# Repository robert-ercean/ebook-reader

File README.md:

# Block Diagram

# Hardware Features – Detailed Description

## 1. Microcontroller – ESP32-C6

- **Processor:** 32-bit RISC-V core, clocked up to 160 MHz.
- **Memory:** 512KB internal SRAM and 8MB external flash memory (model W25Q512JVEIQ).
- **Connectivity:** Supports Wi-Fi 6 (802.11ax), Bluetooth Low Energy 5, and USB 2.0 (full-speed).
- **Interfaces:** SPI, I²C, UART, and multiple available GPIOs.
- **Power Efficiency:** Power-saving modes, including deep sleep.

## 2. E-Paper Display – 7.5”

- **Model:** Waveshare or equivalent, with a resolution of 800×480 pixels.
- **Connection:** 4-wire SPI plus control pins (CS, DC, RST, BUSY).
- **Power Consumption:** Very low in static mode; during refresh, consumption ranges between 15–25mA.

## 3. Environmental Sensor – BME688

- **Measurements:** Temperature, relative humidity, atmospheric pressure, and air quality (eCO2/VOC).
- **Interface:** I²C protocol at 400kHz (SDA/SCL).
- **Power Consumption:** Approx. 2.1µA in standby, with peaks of a few mA when active.

## 4. Power Supply and Management System

- **Battery:** Li-Po 3.7V, 2500mAh capacity.
- **Charging:** MCP73831 – simple and reliable IC for USB-C charging, up to 1A.
- **Monitoring:** MAX17048 – fuel gauge providing voltage and battery level data.
- **Voltage Regulation:** LDO such as XC6220A331MR-G, for a stable 3.3V output.

**Why these components?**
- MCP73831 offers a compact and efficient solution.
- MAX17048 enables precise battery monitoring and low-level warnings.

## 5. Buttons – 3 units

- **Type:** Tactile switch (Panasonic or similar).
- **Purpose:** Menu navigation, page turning, option selection.
- **Connection:** To GPIOs, with hardware (RC) or software debouncing.

## 6. USB-C Connector

- **Purpose:** Power/charging + data transfer via USB 2.0.
- **Protection:** ESD (e.g., USBLC6-2SC6Y) and termination resistors.
- **Options:** Supports firmware updates via USB or OTA via Wi-Fi.

## 7. Qwiic Interface (I²C)

- **Pins:** VCC, GND, SDA, SCL.
- **Functionality:** Quick expansion with additional I²C sensors/modules.

## 8. SD Card Slot – 112A-TAAR-R03

- **Purpose:** Storing e-books, logs, or firmware files.
- **Connection:** SPI or SDIO, depending on implementation.

## 9. Real-Time Clock – DS3231

- **Purpose:** Precise timekeeping, even without main power.
- **Communication:** I²C (shared with other sensors).
- **Backup:** Supercapacitor or secondary battery.

## 10. Additional Memory

- **Model:** W25Q512JVEIQ – external flash memory.
- **Connection:** Dedicated SPI (quad SPI) for firmware and large files.

---

# 4. ESP32-C6 Pin Allocation

| ESP32-C6 Pin | Signal                        | Detailed                                   |
|--------------|-------------------------------|--------------------------------------------|
| GPIO1        | I²C SDA                       | Data line for sensors and RTC              |
| GPIO2        | I²C SCL                       | Clock line for I²C interface               |
| GPIO5        | SPI MISO                      | Data input from e-paper                    |
| GPIO6        | SPI MOSI                      | Data output to e-paper                     |
| GPIO7        | SPI CLK                       | Clock signal for SPI                       |
| GPIO8        | SPI CS (e-paper)              | Chip select for display                    |
| GPIO9        | E-paper DC                    | Switch between data and command modes      |
| GPIO10       | E-paper RST                   | Hardware reset for the display             |
| GPIO11       | E-paper BUSY                  | Status signal (busy/free)                  |
| GPIO12       | Button 1                      | Digital input for NEXT                     |
| GPIO13       | Button 2                      | Digital input for PREV                     |
| GPIO14       | Button 3                      | Digital input for OK/MENU                  |
| GPIO15       | MAX17048 ALERT (optional)     | Low battery alert                          |
| GPIO16       | USB D+                        | USB data line (fixed pin)                  |
| GPIO17       | USB D-                        | USB data line (fixed pin)                  |
| GPIO18       | Status LED (optional)         | Visual indicator for various states        |
| GPIO19       | SD Card CS                    | Chip select for SD card (SPI)              |
| GPIO20       | SD Card MISO                  | Data received from SD card                 |
| GPIO21       | SD Card MOSI                  | Data sent to SD card                       |
| GPIO4        | SD Card CLK                   | SPI clock line for SD communication        |

---

# Power Consumption Estimate

| Module                | Typical Consumption              |
|------------------------|----------------------------------|
| ESP32-C6 active        | ~80mA with Wi-Fi / <10mA idle   |
| E-paper (refresh)      | 15–25mA                         |
| BME688 active          | up to 3.6mA / 2.1µA standby     |
| MAX17048               | Approx. 50µA                    |
| DS3231                 | ~3.5mA active / <1µA backup     |
| MCP73831               | Varies based on charging current|

**Usage Scenarios:**
- In **deep sleep**, total consumption can drop below 100µA.
- In active mode with Wi-Fi and screen refresh, consumption may reach 100–150mA.
- A 2500mAh battery allows for **weeks of operation** in predominantly passive mode (static display, infrequent Wi-Fi activity).

---

# Bill of Materials:

| Component | Type | Marketplace | Datasheet |
|----------|------|-------------|-----------|
| EAGLE-LTSPICE_CC0402 | Capacitor | [Link](https://eu.mouser.com/ProductDetail/KEMET/C0402C475K8PACTU?qs=ulEaXIWI0c9ebKRT3r3htg%3D%3D) | [Datasheet](https://eu.mouser.com/datasheet/2/447/KEM_C1006_X5R_SMD-3316465.pdf) |
| ESP32_WROVER_EAGLE-LTSPICE_RR0402 | Resistor | [Link](https://eu.mouser.com/ProductDetail/Vishay-Beyschlag/MCS04020D9101BE000?qs=sGAEpiMZZMvdGkrng054twKDKoBh%252BscnK%2FuqkNk9X%252BqO%2Fz5%2F0u93Ow%3D%3D) | [Datasheet](https://www.vishay.com/docs/28700/mcx0x0xpre.pdf) |
| RCL_CPOL-EUCT3528 | Capacitor | [Link](https://eu.mouser.com/ProductDetail/Nichicon/LGN2W101MELA25?qs=Fe64Qgzkstf1zMszMsgRoA%3D%3D) | [Datasheet](https://eu.mouser.com/datasheet/2/293/e_lgn-3082370.pdf) |
| ADAFRUIT_LEDCHIP-LED0603 | LED | [Link](https://eu.mouser.com/ProductDetail/ams-OSRAM/KG-EELP41.22-PHRH-35-A8J8-20-R18?qs=ZcfC38r4Posajg8ZvCDQkg%3D%3D) | [Datasheet](https://eu.mouser.com/datasheet/2/588/KG_EELP41_22_EN-3572852.pdf) |
| CPH3225A | Capacitor | [Link](https://eu.mouser.com/ProductDetail/Seiko-Semiconductors/CPH3225A?qs=3etwrb1wR%252BhUOph6lAO7eg%3D%3D) | [Datasheet](https://eu.mouser.com/datasheet/2/360/Seiko_Instruments_MicroBattery_E_20230330_2024Jan_-3561061.pdf) |
| ESP32_WROVER_SPARKFUN-DISCRETESEMI_MOSFET_PCH-DMG2305UX-7 | Transistor | [Link](https://eu.mouser.com/ProductDetail/Diodes-Incorporated/DMG2305UX-7?qs=L1DZKBg7t5F%2FNBHrjfxC%252Bg%3D%3D) | [Datasheet](https://www.diodes.com/assets/Datasheets/DMG2305UX.pdf) |
| ESP32_WROVER_AVX---SD0805S020S1R0_AVX_SD0805S020S1R0_0_0AVX_SD0805S020S1R0_0_0 | Diode | [Link](https://eu.mouser.com/ProductDetail/ROHM-Semiconductor/SCS310AMC7G?qs=iLKYxzqNS75xiccEgNnX2g%3D%3D) | [Datasheet](https://fscdn.rohm.com/en/products/databook/datasheet/discrete/sic/sbd/scs310am-e.pdf) |
| SI1308EDL-T1-GE3 | Transistor | [Link](https://eu.mouser.com/ProductDetail/Vishay-Semiconductors/SI1308EDL-T1-GE3?qs=bX1%252BNvsK%2FBramh9tgpOaEw%3D%3D) | [Datasheet](https://www.vishay.com/docs/63399/si1308edl.pdf) |
| ESP32C6_VARISTORCN1812 | Varistor | [Link](https://eu.mouser.com/ProductDetail/Schurter/PFMF.050.2?qs=1auRipcfynCums5v1iucSA%3D%3D) | [Datasheet](https://eu.mouser.com/datasheet/2/358/typ_PFMF-1275918.pdf) |
| ESP32_WROVER_BME680_BME680 | Integrated Environmental Unit | [Link](https://eu.mouser.com/ProductDetail/M5Stack/U001-C?qs=e8oIoAS2J1R2mB7ZY1%252BSZg%3D%3D) | [Datasheet](https://docs.m5stack.com/en/unit/envIII) |
| ESP32-C6-WROOM-1-N8 | MicroController | [Link](https://eu.mouser.com/ProductDetail/Espressif-Systems/ESP32-C6?qs=Imq1NPwxi75noDtUpuVuWw%3D%3D) | [Datasheet](https://eu.mouser.com/datasheet/2/891/esp32_c6_datasheet_en-3304070.pdf) |
| 744043680IND_4828-WE-TPC_WRE | Inductor | [Link](https://eu.mouser.com/ProductDetail/Wurth-Elektronik/744043680?qs=PGXP4M47uW6VkZq%252BkzjrHA%3D%3D) | [Datasheet](https://www.we-online.com/components/products/datasheet/744043680.pdf) |
| SI1308EDL-T1-GE3 | Transistor | [Link](https://eu.mouser.com/ProductDetail/Vishay-Semiconductors/SI1308EDL-T1-GE3?qs=bX1%252BNvsK%2FBramh9tgpOaEw%3D%3D) | [Datasheet](https://www.vishay.com/docs/63399/si1308edl.pdf) |
| BD5229G-TR | Voltage Detector | [Link](https://eu.mouser.com/ProductDetail/ROHM-Semiconductor/BD5229G-TR?qs=sGAEpiMZZMutXGli8Ay4kAMqIQqqdOUlDFcDfPDPIK4%3D) | [Datasheet](https://fscdn.rohm.com/en/products/databook/datasheet/ic/power/voltage_detector/bd52xxg-e.pdf) |
| DS3231SN# | RTC Module | [Link](https://eu.mouser.com/ProductDetail/Analog-Devices-Maxim-Integrated/DS3231SN?qs=1eQvB6Dk1vhUlr8%2FOrV0Fw%3D%3D) | [Datasheet](https://eu.mouser.com/datasheet/2/609/DS3231-3421123.pdf) |
| USBLC6-2SC6Y | ESD Protection | [Link](https://eu.mouser.com/ProductDetail/STMicroelectronics/USBLC6-2SC6Y?qs=gNDSiZmRJS%2FOgDexvXkdow%3D%3D) | [Datasheet](https://eu.mouser.com/datasheet/2/389/usblc6_2sc6y-1852505.pdf) |
| W25Q512JVEIQ | Flash Memory | [Link](https://eu.mouser.com/ProductDetail/Winbond/W25Q512JVEIQ?qs=l7cgNqFNU1jw6svr3at6tA%3D%3D) | [Datasheet](https://eu.mouser.com/datasheet/2/949/Winbond_W25Q512JV_Datasheet-3240039.pdf) |
| SAMACSYS_PARTS_USB4110-GF-A | USB Connector | [Link](https://eu.mouser.com/ProductDetail/GCT/USB4110-GF-A?qs=KUoIvG%2F9IlYiZvIXQjyJeA%3D%3D) | [Datasheet](https://eu.mouser.com/datasheet/2/837/GCT_USB4110_Product_Drawing___20k_cycles-3455479.pdf) |
| FH34SRJ | E-Paper Display Header | [Link](https://eu.mouser.com/ProductDetail/Hirose-Connector/FH34SRJ-7S-0.5SH50?qs=vcbW%252B4%252BSTIqHa4IamMh36g%3D%3D) | [Datasheet](https://eu.mouser.com/datasheet/2/185/FH34SRJ_7S_0_5SH_50__CL0580_1200_0_50_2DDrawing_00-1615127.pdf) |
| MAX17048G+T10 | Battery Management | [Link](https://eu.mouser.com/ProductDetail/Analog-Devices-Maxim-Integrated/MAX17048G%2bT10?qs=D7PJwyCwLAoGnnn8jEPRBQ%3D%3D) | [Datasheet](https://eu.mouser.com/datasheet/2/609/MAX17048_MAX17049-3469099.pdf) |
| MCP73831 | Battery Controller | [Link](https://eu.mouser.com/ProductDetail/Microchip-Technology/MCP73831T-2ATI-MC?qs=yUQqVecv4qs9k7ug0bEXiw%3D%3D) | [Datasheet](https://eu.mouser.com/datasheet/2/268/MCP73831_Family_Data_Sheet_DS20001984H-3441711.pdf) |
| 112A-TAAR-R03_ATTEND | SD Card Mount | [Link](https://store.comet.srl.ro/Catalogue/Product/43497/) | [Datasheet](https://store.comet.srl.ro/Catalogue/Product/43497/) |
| XC6220A331MR-G | LDO Voltage Regulator | [Link](https://eu.mouser.com/ProductDetail/Torex-Semiconductor/XC6220A331MR-G?qs=AsjdqWjXhJ8ZSWznL1J0gg%3D%3D) | [Datasheet](https://eu.mouser.com/datasheet/2/760/xc6220-3371556.pdf) |

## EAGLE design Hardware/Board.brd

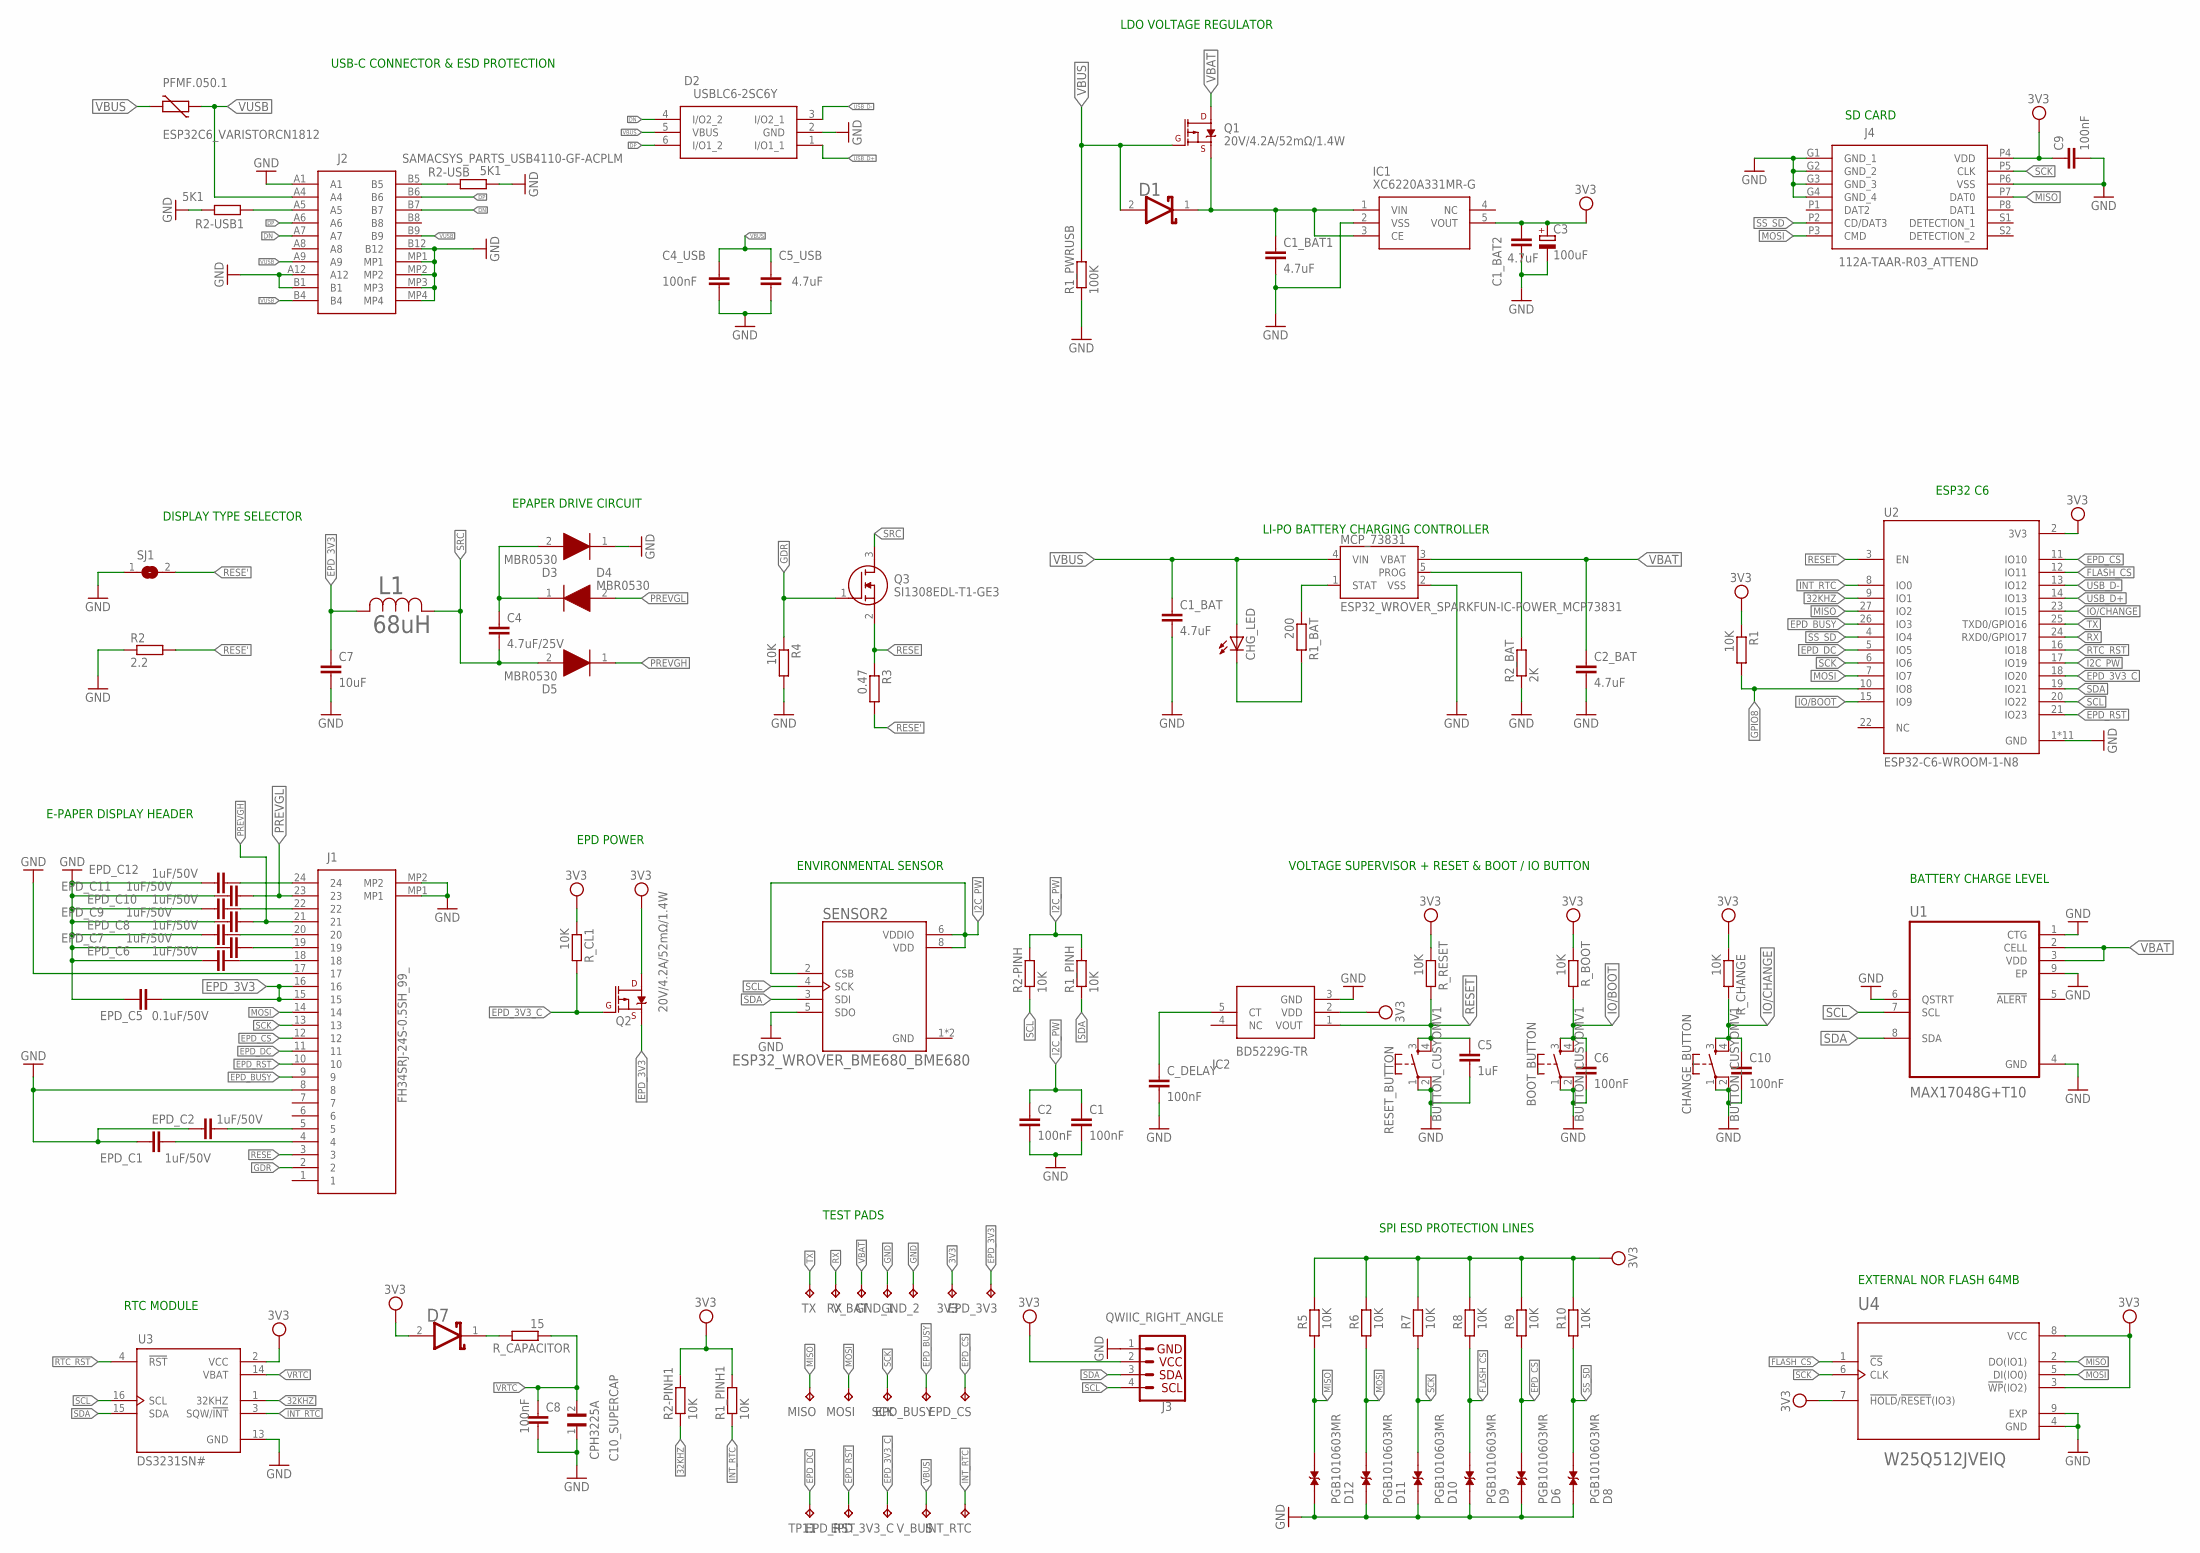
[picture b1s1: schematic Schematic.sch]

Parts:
3V3: TPTP20R; TP20R
BOOT_BUTTON: BUTTON_CUSYOMV1; MYBUTTON
C1, C2, C4_USB, C6, C8, C9, C10: 100nF; EAGLE-LTSPICE_C0402
C1_BAT, C1_BAT1, C1_BAT2, C2_BAT, C5_USB: 4.7uF; EAGLE-LTSPICE_C0402
C3: 100uF; RCL_CT3528
C4: 4.7uF/25V; EAGLE-LTSPICE_C0402
C5: 1uF; EAGLE-LTSPICE_C0402
C7: 10uF; EAGLE-LTSPICE_C0402
C10_SUPERCAP: CPH3225A; CAPCP3225X100N
CHANGE_BUTTON: BUTTON_CUSYOMV1; MYBUTTON
CHG_LED: ADAFRUIT_LEDCHIP-LED0603; ADAFRUIT_CHIP-LED0603
C_DELAY: 100nF; EAGLE-LTSPICE_C0402
D1, D7: ESP32_WROVER_AVX---SD0805S020S1R0_AVX_SD0805S020S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; ESP32_WROVER_AVX---SD0805S020S1R0_AVX_SD0805S020S1R0_0
D2: USBLC6-2SC6Y; SOT95P280X145-6N
D3, D4, D5: MBR0530; SOD3716X135N
D6, D8, D9, D10, D11, D12: PGB1010603MR; DIOC1608X36N
EPD_3V3, EPD_3V3_C: TPTP20R; TP20R
EPD_BUSY: TPTP20R; TP20R
EPD_C1, EPD_C2, EPD_C6, EPD_C7, EPD_C8, EPD_C9, EPD_C10, EPD_C11, EPD_C12: 1uF/50V; EAGLE-LTSPICE_C0402
EPD_C5: 0.1uF/50V; EAGLE-LTSPICE_C0402
EPD_CS: TPTP20R; TP20R
EPD_RST: TPTP20R; TP20R
GND_1, GND_2: TPTP20R; TP20R
IC1: XC6220A331MR-G; SOT95P280X120-5N
IC2: BD5229G-TR; SOT95P280X125-5N
INT_RTC: TPTP20R; TP20R
J1: FH34SRJ-24S-0.5SH_99_; FH34SRJ24S05SH99
J2: SAMACSYS_PARTS_USB4110-GF-ACPLM; SAMACSYS_PARTS_USB4110GFA
J3: QWIIC_RIGHT_ANGLE; JST04_1MM_RA
J4: 112A-TAAR-R03_ATTEND; 112ATAARR03ATTEND
L1: 68uH; IND_4828-WE-TPC_WRE
MCP_73831: ESP32_WROVER_SPARKFUN-IC-POWER_MCP73831; ESP32_WROVER_SPARKFUN-IC-POWER_SOT23-5
MISO: TPTP20R; TP20R
MOSI: TPTP20R; TP20R
PFMF.050.1: ESP32C6_VARISTORCN1812; ESP32C6_VARISTOR_CT/CN1812
Q1, Q2: 20V/4.2A/52mΩ/1.4W; ESP32_WROVER_SPARKFUN-DISCRETESEMI_SOT23-3
Q3: SI1308EDL-T1-GE3; SOT65P210X110-3N
R1, R1_PINH, R1_PINH1, R2-PINH, R2-PINH1, R4, R5, R6, R7, R8, R9, R10: 10K; ESP32_WROVER_EAGLE-LTSPICE_R0402
R1_BAT: 200; ESP32_WROVER_EAGLE-LTSPICE_R0402
R1_PWRUSB: 100K; ESP32_WROVER_EAGLE-LTSPICE_R0402
R2: 2.2; ESP32_WROVER_EAGLE-LTSPICE_R0402
R2-USB, R2-USB1: 5K1; ESP32_WROVER_EAGLE-LTSPICE_R0402
R2_BAT: 2K; ESP32_WROVER_EAGLE-LTSPICE_R0402
R3: 0.47; ESP32_WROVER_EAGLE-LTSPICE_R0402
RESET_BUTTON: BUTTON_CUSYOMV1; MYBUTTON
RX: TPTP20R; TP20R
R_BOOT: 10K; ESP32_WROVER_EAGLE-LTSPICE_R0402
R_CAPACITOR: 15; ESP32_WROVER_EAGLE-LTSPICE_R0402
R_CHANGE: 10K; ESP32_WROVER_EAGLE-LTSPICE_R0402
R_CL1: 10K; ESP32_WROVER_EAGLE-LTSPICE_R0402
R_RESET: 10K; ESP32_WROVER_EAGLE-LTSPICE_R0402
SCK: TPTP20R; TP20R
SENSOR2: ESP32_WROVER_BME680_BME680; ESP32_WROVER_BME680_PSON80P300X300X100-8N
SJ1: SJ
TP11: TPTP20R; TP20R
TX: TPTP20R; TP20R
U1: MAX17048G+T10; SON50P200X200X80-9N
U2: ESP32-C6-WROOM-1-N8; XCVR_ESP32-C6-WROOM-1-N8
U3: DS3231SN#; SOIC127P1032X265-16N
U4: W25Q512JVEIQ; SON127P600X800X80-9N
V_BAT: TPTP20R; TP20R
V_BUS: TPTP20R; TP20R

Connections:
3V3: 3V3.TP, C1_BAT2.1, C3.+, C9.1, D7.2 (ANODE), IC1.5 (VOUT), IC2.2 (VDD), J3.2, J4.P4 (VDD), Q2.3 (D), R1.1, R1_PINH1.2, R2-PINH1.2, R5.2, R6.2, R7.2, R8.2, R9.2, R10.2, R_BOOT.1, R_CHANGE.1, R_CL1.1, R_RESET.1, U2.2 (3V3), U3.2 (VCC), U4.3 (!WP!(IO2)), U4.7 (!HOLD!/!RESET!(IO3)), U4.8 (VCC)
32KHZ: R2-PINH1.1, U2.9 (IO1), U3.1 (32KHZ)
DN: D2.4 (I/O2_2), J2.A7, J2.B7
DP: D2.6 (I/O1_2), J2.A6, J2.B6
EPD_3V3: C7.1, EPD_3V3.TP, EPD_C5.1, J1.15, J1.16, L1.2, Q2.2 (S)
EPD_3V3_C: EPD_3V3_C.TP, Q2.1 (G), R_CL1.2, U2.18 (IO20)
EPD_BUSY: EPD_BUSY.TP, J1.9, U2.26 (IO3)
EPD_CS: D6.2, EPD_CS.TP, J1.12, R9.1, U2.11 (IO10)
EPD_DC: J1.11, TP11.TP, U2.5 (IO5)
EPD_RST: EPD_RST.TP, J1.10, U2.21 (IO23)
FLASH_CS: D9.2, R8.1, U2.12 (IO11), U4.1 (!CS)
GDR: J1.2, Q3.1 (G), R4.1
GND: BOOT_BUTTON.1, BOOT_BUTTON.2, C1.2, C1_BAT.2, C1_BAT1.2, C1_BAT2.2, C2.2, C2_BAT.2, C3.-, C4_USB.2, C5.2, C5_USB.2, C6.2, C7.2, C8.2, C9.2, C10.2, C10_SUPERCAP.1, CHANGE_BUTTON.1, CHANGE_BUTTON.2, C_DELAY.2, D2.2 (GND), D3.1 (K), D6.1, D8.1, D9.1, D10.1, D11.1, D12.1, EPD_C1.2, EPD_C2.2, EPD_C5.2, EPD_C6.2, EPD_C7.2, EPD_C8.2, EPD_C9.2, EPD_C10.2, EPD_C11.2, EPD_C12.2, GND_1.TP, GND_2.TP, IC1.2 (VSS), IC2.3 (GND), J1.8, J1.17, J1.MP1, J1.MP2, J2.A1, J2.A12, J2.B1, J2.B12, J2.MP1, J2.MP2, J2.MP3, J2.MP4, J3.1, J4.G1 (GND_1), J4.G2 (GND_2), J4.G3 (GND_3), J4.G4 (GND_4), J4.P6 (VSS), MCP_73831.2 (VSS), R1_PWRUSB.1, R2.1, R2-USB.2, R2-USB1.1, R2_BAT.1, R4.2, RESET_BUTTON.1, RESET_BUTTON.2, SENSOR2.1 (GND), SENSOR2.5 (SDO), SENSOR2.7 (GND), SJ1.1, U1.1 (CTG), U1.4 (GND), U1.6 (QSTRT), U1.9 (EP), U2.1 (GND), U2.28 (GND), U2.29_1 (GND), U2.29_2 (GND), U2.29_3 (GND), U2.29_4 (GND), U2.29_5 (GND), U2.29_6 (GND), U2.29_7 (GND), U2.29_8 (GND), U2.29_9 (GND), U3.13 (GND), U4.4 (GND), U4.9 (EXP)
GPIO8: R1.2, U2.10 (IO8)
I2C_PW: C1.1, C2.1, R1_PINH.2, R2-PINH.2, SENSOR2.2 (CSB), SENSOR2.6 (VDDIO), SENSOR2.8 (VDD), U2.17 (IO19)
INT_RTC: INT_RTC.TP, R1_PINH1.1, U2.8 (IO0), U3.3 (SQW/!INT)
IO/BOOT: BOOT_BUTTON.3, BOOT_BUTTON.4, C6.1, R_BOOT.2, U2.15 (IO9)
IO/CHANGE: C10.1, CHANGE_BUTTON.3, CHANGE_BUTTON.4, R_CHANGE.2, U2.23 (IO15)
MISO: D12.2, J4.P7 (DAT0), MISO.TP, R5.1, U2.27 (IO2), U4.2 (DO(IO1))
MOSI: D11.2, J1.14, J4.P3 (CMD), MOSI.TP, R6.1, U2.7 (IO7), U4.5 (DI(IO0))
unnamed: C1_BAT1.1, D1.1 (CATHODE), IC1.1 (VIN), IC1.3 (CE), Q1.2 (S)
unnamed: MCP_73831.1 (STAT), R1_BAT.1
unnamed: CHG_LED.C, R1_BAT.2
unnamed: MCP_73831.5 (PROG), R2_BAT.2
unnamed: C_DELAY.1, IC2.5 (CT)
unnamed: J2.A5, R2-USB1.2
unnamed: J2.B5, R2-USB.1
unnamed: C4.1, D3.2 (A), D4.1 (K)
unnamed: EPD_C2.1, J1.5
unnamed: EPD_C12.1, J1.24
unnamed: EPD_C1.1, J1.4
unnamed: D7.1 (CATHODE), R_CAPACITOR.2
unnamed: EPD_C10.1, J1.22
unnamed: EPD_C8.1, J1.20
unnamed: EPD_C7.1, J1.19
unnamed: EPD_C6.1, J1.18
PREVGH: D5.1 (K), EPD_C9.1, J1.21
PREVGL: D4.2 (A), EPD_C11.1, J1.23
RESE: J1.3, Q3.2 (S), R3.1
RESE': R2.2, R3.2, SJ1.2
RESET: C5.1, IC2.1 (VOUT), RESET_BUTTON.3, RESET_BUTTON.4, R_RESET.2, U2.3 (EN)
RTC_RST: U2.16 (IO18), U3.4 (!RST)
RX: RX.TP, U2.24 (RXD0/GPIO17)
SCK: D10.2, J1.13, J4.P5 (CLK), R7.1, SCK.TP, U2.6 (IO6), U4.6 (CLK)
SCL: J3.4, R2-PINH.1, SENSOR2.4 (SCK), U1.7 (SCL), U2.20 (IO22), U3.16 (SCL)
SDA: J3.3, R1_PINH.1, SENSOR2.3 (SDI), U1.8 (SDA), U2.19 (IO21), U3.15 (SDA)
SRC: C4.2, D5.2 (A), L1.1, Q3.3 (D)
SS_SD: D8.2, J4.P2 (CD/DAT3), R10.1, U2.4 (IO4)
TX: TX.TP, U2.25 (TXD0/GPIO16)
USB_D+: D2.1 (I/O1_1), U2.14 (IO13)
USB_D-: D2.3 (I/O2_1), U2.13 (IO12)
VBAT: C2_BAT.1, MCP_73831.3 (VBAT), Q1.3 (D), U1.2 (CELL), U1.3 (VDD), V_BAT.TP
VBUS: C1_BAT.1, C4_USB.1, C5_USB.1, CHG_LED.A, D1.2 (ANODE), D2.5 (VBUS), MCP_73831.4 (VIN), PFMF.050.1.2, Q1.1 (G), R1_PWRUSB.2, V_BUS.TP
VRTC: C8.1, C10_SUPERCAP.2, R_CAPACITOR.1, U3.14 (VBAT)
VUSB: J2.A4, J2.A9, J2.B4, J2.B9, PFMF.050.1.1

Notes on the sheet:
SD CARD
LI-PO BATTERY CHARGING CONTROLLER
ESP32 C6
VOLTAGE SUPERVISOR + RESET & BOOT / IO BUTTON
ENVIRONMENTAL SENSOR
EPD POWER
E-PAPER DISPLAY HEADER
RTC MODULE
TEST PADS
EXTERNAL NOR FLASH 64MB
SPI ESD PROTECTION LINES
LDO VOLTAGE REGULATOR
USB-C CONNECTOR & ESD PROTECTION
DISPLAY TYPE SELECTOR
EPAPER DRIVE CIRCUIT
BATTERY CHARGE LEVEL

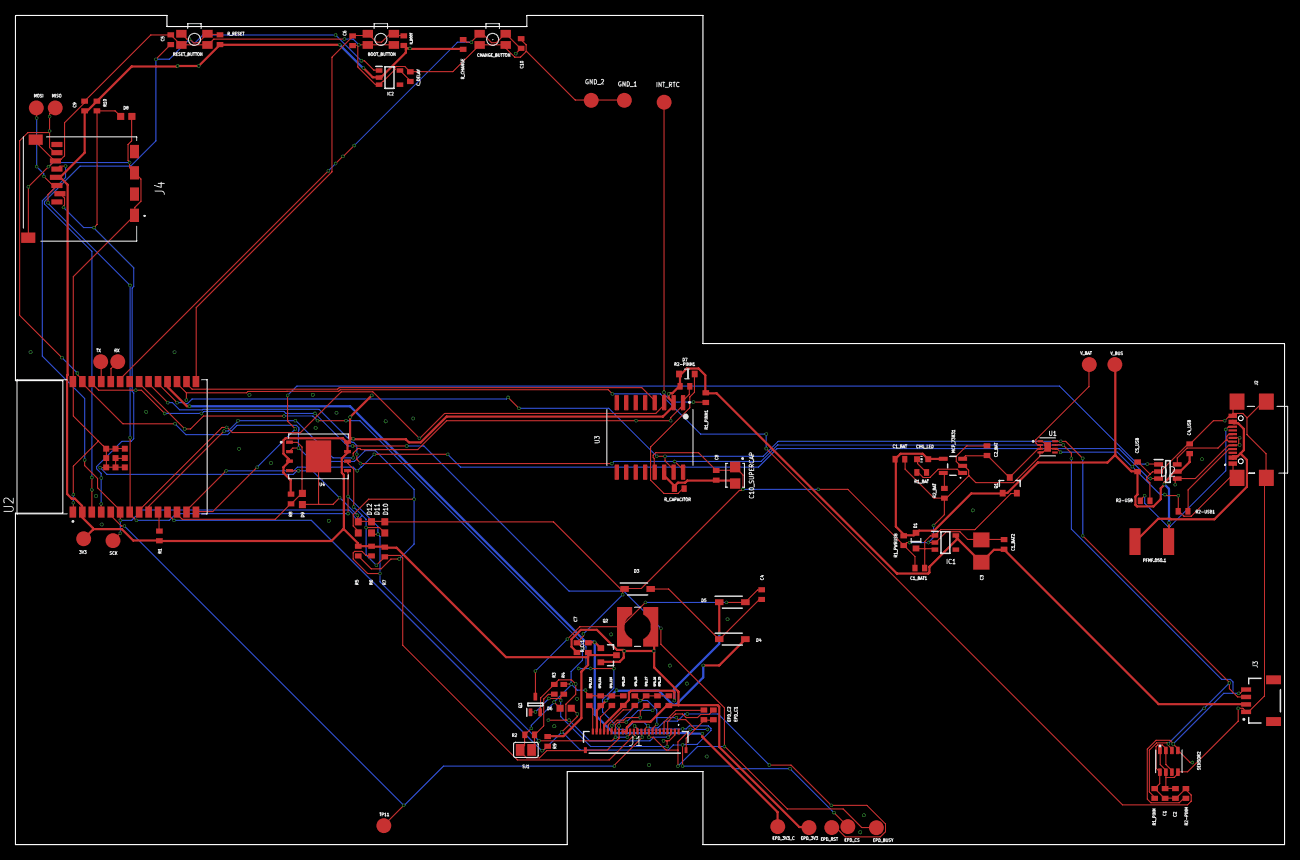
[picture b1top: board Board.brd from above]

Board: 2 copper layers, 170.2 x 111.2 mm, 103 parts (0 on the bottom side), 55 nets.

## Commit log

2025-04-06 Added all files
2025-04-11 adjusted readme
2025-04-13 Fixed issues
2025-04-14 updated sschematic and board
2025-04-14 new board

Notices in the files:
parts and their libraries:
COPYRIGHT: Copyright (C) 2024 Ultra Librarian. All rights reserved.
